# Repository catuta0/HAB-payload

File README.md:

# hab-payload

Carrier PCB for a high-altitude balloon payload. An ESP32 DevKitC V4 (WROOM-32) plugs into the board together with breakout modules for GPS (NEO-8M, I2C or UART header, fit only one), INA260 power monitor, BME280, LSM6DSOX IMU, MAX31855 thermocouple amplifier, RFM95 LoRa radio and an SPI SD card. All modules sit on female headers. The ESP32 is powered from 3.3 V only; its 5 V pin is not connected.

Power comes from a 3S Li-ion pack (9 to 12.6 V) on J1, through a 1.5 A PTC, a 13 V TVS and a P-MOSFET reverse polarity switch, into two TPS62160 bucks at 3.3 V and 5 V. Each buck output goes through a pi filter (ferrite, X7R, solid polymer) with the feedback taken before the ferrite, and the GPS, RFM95 and MAX31855 supplies have their own local ferrite. All capacitors are X7R or solid polymer, with no liquid electrolytics, for operation below 0 C.

The fast SPI lines run on the top layer with 33 ohm series termination at the source (ESP32 for SCK and MOSI, SD module for MISO). Ground is poured on both layers and stitched, SMD pads connect solid to the pour. Test points TP1 to TP4 give VBAT, 3V3, 5V and GND.

Open hardware/pcbgalapagos.kicad_pro in KiCad 10. The project symbol library (galapagos.kicad_sym) and footprint library (galapagos_fp.pretty) are registered relative to the project folder. BOM.csv lists every part with its Mouser link (the breakout modules are bought separately), and docs/firmware_changes.md lists what the firmware has to change for this board.

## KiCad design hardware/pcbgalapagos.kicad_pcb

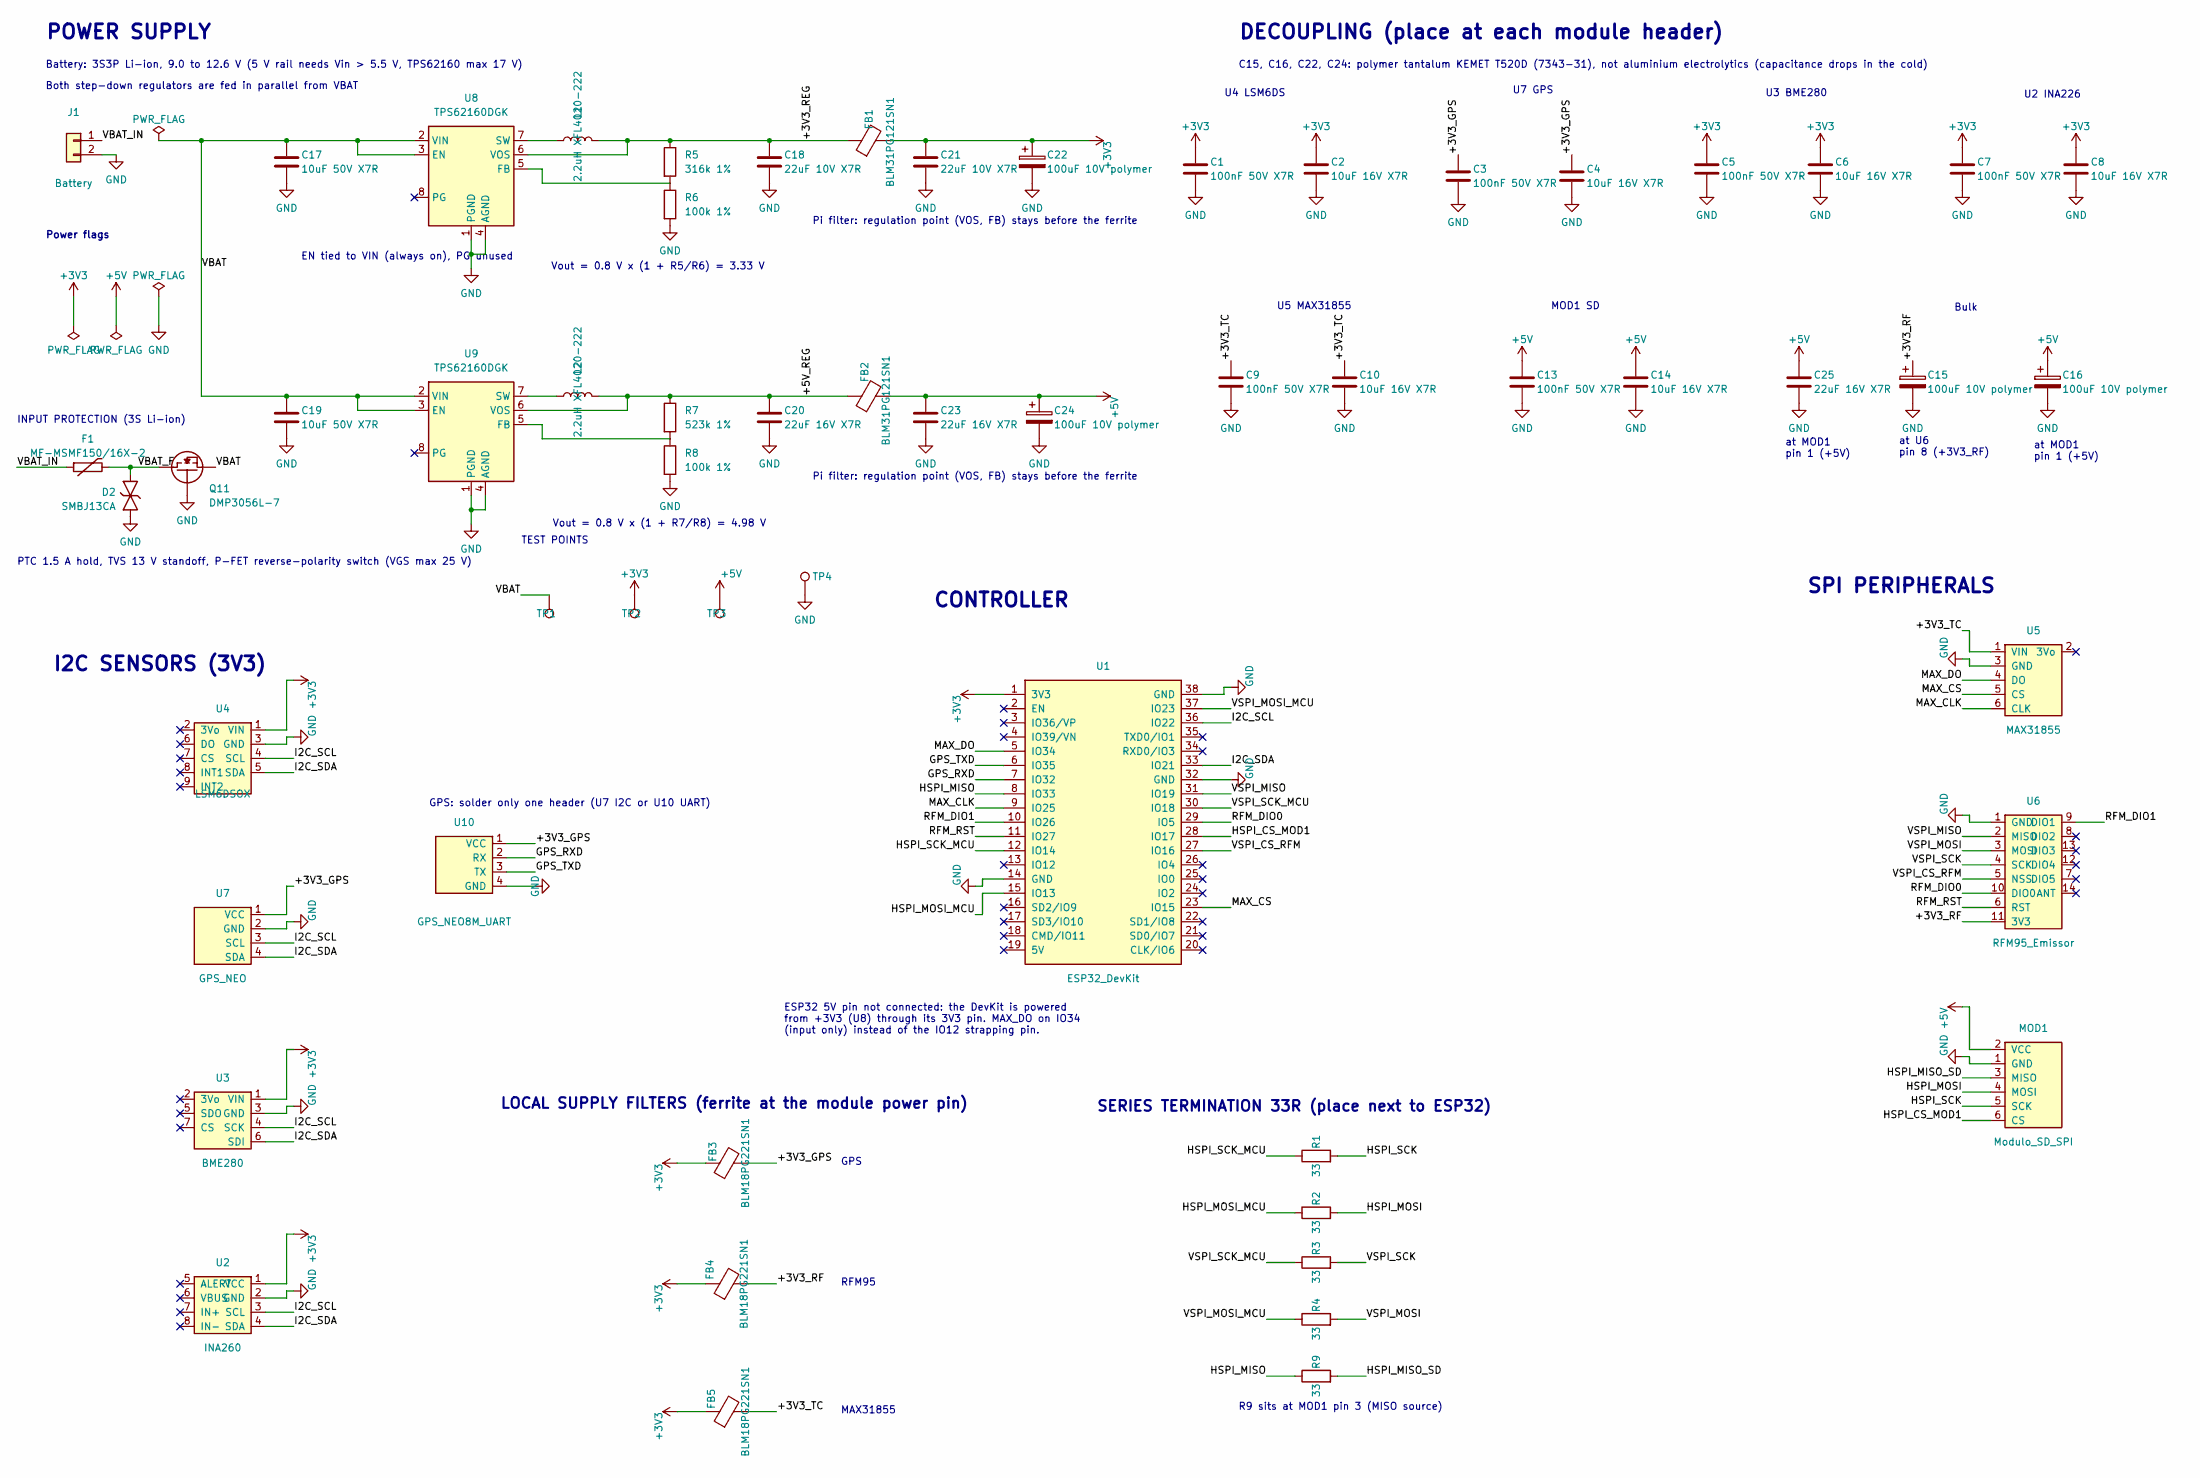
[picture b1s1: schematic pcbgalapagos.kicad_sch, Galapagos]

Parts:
C1, C3, C5, C7, C9, C13: 100nF 50V X7R; C_0805_2012Metric
C2, C4, C6, C8, C10, C14: 10uF 16V X7R; C_0805_2012Metric
C15, C16, C22, C24: 100uF 10V polymer; CP_EIA-7343-31_Kemet-D
C17, C19: 10uF 50V X7R; C_1210_3225Metric
C18, C21: 22uF 10V X7R; C_1206_3216Metric
C20, C23, C25: 22uF 16V X7R; C_1206_3216Metric
D2: SMBJ13CA; D_SMB
F1: MF-MSMF150/16X-2; Fuse_1812_4532Metric
FB1, FB2: BLM31PG121SN1; L_1206_3216Metric
FB3, FB4, FB5: BLM18PG221SN1; L_0603_1608Metric
J1: Battery; JST_XH_B2B-XH-A_1x02_P2.50mm_Vertical
L1, L2: 2.2uH XFL4020-222; L_Coilcraft_XxL4020
MOD1: Modulo_SD_SPI; PinHeader_1x06_P2.54mm_Vertical
Q11: DMP3056L-7; SOT-23
R1, R2, R3, R4, R9: 33; R_0805_2012Metric
R5: 316k 1%; R_0805_2012Metric
R6, R8: 100k 1%; R_0805_2012Metric
R7: 523k 1%; R_0805_2012Metric
TP1, TP2, TP3, TP4: TestPoint; TestPoint_Pad_D1.5mm
U1: ESP32_DevKit; ESP32_DevKitC_V4_38
U2: INA260; Adafruit_INA260_Header
U3: BME280; Adafruit_BME280_Header
U4: LSM6DSOX; Adafruit_LSM6DSOX_Header
U5: MAX31855; Adafruit_MAX31855_Header
U6: RFM95_Emissor; RFM9x_Breakout_attexx
U7: GPS_NEO; GPS_I2C_Header_1x04
U8, U9: TPS62160DGK; MSOP-8_3x3mm_P0.65mm
U10: GPS_NEO8M_UART; GPS_NEO8M_UART_Header_1x04

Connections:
+3V3: C1.1, C2.1, C5.1, C6.1, C7.1, C8.1, C21.1, C22.1, FB1.2, FB3.1, FB4.1, FB5.1, TP2.1, U1.1 (3V3), U2.1 (VCC), U3.1 (VIN), U4.1 (VIN)
+3V3_GPS: C3.1, C4.1, FB3.2, U7.1 (VCC), U10.1 (VCC)
+3V3_REG: C18.1, FB1.1, L1.2, R5.1, U8.6 (VOS)
+3V3_RF: C15.1, FB4.2, U6.11 (3V3)
+3V3_TC: C9.1, C10.1, FB5.2, U5.1 (VIN)
+5V: C13.1, C14.1, C16.1, C23.1, C24.1, C25.1, FB2.2, MOD1.2 (VCC), TP3.1
+5V_REG: C20.1, FB2.1, L2.2, R7.1, U9.6 (VOS)
GND: C1.2, C2.2, C3.2, C4.2, C5.2, C6.2, C7.2, C8.2, C9.2, C10.2, C13.2, C14.2, C15.2, C16.2, C17.2, C18.2, C19.2, C20.2, C21.2, C22.2, C23.2, C24.2, C25.2, D2.2 (A2), J1.2, MOD1.1 (GND), Q11.1 (G), R6.2, R8.2, TP4.1, U1.14 (GND), U1.32 (GND), U1.38 (GND), U2.2 (GND), U3.3 (GND), U4.3 (GND), U5.3 (GND), U6.1 (GND), U7.2 (GND), U8.1 (PGND), U8.4 (AGND), U9.1 (PGND), U9.4 (AGND), U10.4 (GND)
GPS_RXD: U1.7 (IO32), U10.2 (RX)
GPS_TXD: U1.6 (IO35), U10.3 (TX)
HSPI_CS_MOD1: MOD1.6 (CS), U1.28 (IO17)
HSPI_MISO: R9.1, U1.8 (IO33)
HSPI_MISO_SD: MOD1.3 (MISO), R9.2
HSPI_MOSI: MOD1.4 (MOSI), R2.2
HSPI_MOSI_MCU: R2.1, U1.15 (IO13)
HSPI_SCK: MOD1.5 (SCK), R1.2
HSPI_SCK_MCU: R1.1, U1.12 (IO14)
I2C_SCL: U1.36 (IO22), U2.3 (SCL), U3.4 (SCK), U4.4 (SCL), U7.3 (SCL)
I2C_SDA: U1.33 (IO21), U2.4 (SDA), U3.6 (SDI), U4.5 (SDA), U7.4 (SDA)
MAX_CLK: U1.9 (IO25), U5.6 (CLK)
MAX_CS: U1.23 (IO15), U5.5 (CS)
MAX_DO: U1.5 (IO34), U5.4 (DO)
unnamed: R5.2, R6.1, U8.5 (FB)
unnamed: L1.1, U8.7 (SW)
unnamed: R7.2, R8.1, U9.5 (FB)
unnamed: L2.1, U9.7 (SW)
RFM_DIO0: U1.29 (IO5), U6.10 (DIO0)
RFM_DIO1: U1.10 (IO26), U6.9 (DIO1)
RFM_RST: U1.11 (IO27), U6.6 (RST)
VBAT: C17.1, C19.1, Q11.2 (S), TP1.1, U8.2 (VIN), U8.3 (EN), U9.2 (VIN), U9.3 (EN)
VBAT_F: D2.1 (A1), F1.2, Q11.3 (D)
VBAT_IN: F1.1, J1.1
VSPI_CS_RFM: U1.27 (IO16), U6.5 (NSS)
VSPI_MISO: U1.31 (IO19), U6.2 (MISO)
VSPI_MOSI: R4.2, U6.3 (MOSI)
VSPI_MOSI_MCU: R4.1, U1.37 (IO23)
VSPI_SCK: R3.2, U6.4 (SCK)
VSPI_SCK_MCU: R3.1, U1.30 (IO18)

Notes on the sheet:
Vout = 0.8 V x (1 + R5/R6) = 3.33 V
CONTROLLER
RFM95
Bulk
PTC 1.5 A hold, TVS 13 V standoff, P-FET reverse-polarity switch (VGS max 25 V)
Vout = 0.8 V x (1 + R7/R8) = 4.98 V
MAX31855
Power flags
GPS
U2 INA226
at MOD1 pin 1 (+5V)
INPUT PROTECTION (3S Li-ion)
MOD1 SD
SPI PERIPHERALS
SERIES TERMINATION 33R (place next to ESP32)
U7 GPS
U3 BME280
C15, C16, C22, C24: polymer tantalum KEMET T520D (7343-31), not aluminium electrolytics (capacitance drops in the cold)
Battery: 3S3P Li-ion, 9.0 to 12.6 V (5 V rail needs Vin > 5.5 V, TPS62160 max 17 V)
at U6 pin 8 (+3V3_RF)
DECOUPLING (place at each module header)
Both step-down regulators are fed in parallel from VBAT
I2C SENSORS (3V3)
Pi filter: regulation point (VOS, FB) stays before the ferrite
POWER SUPPLY
U5 MAX31855
LOCAL SUPPLY FILTERS (ferrite at the module power pin)
EN tied to VIN (always on), PG unused
U4 LSM6DS
ESP32 5V pin not connected: the DevKit is powered from +3V3 (U8) through its 3V3 pin. MAX_DO on IO34 (input only) instead of the IO12 strapping pin.
GPS: solder only one header (U7 I2C or U10 UART)
R9 sits at MOD1 pin 3 (MISO source)
TEST POINTS

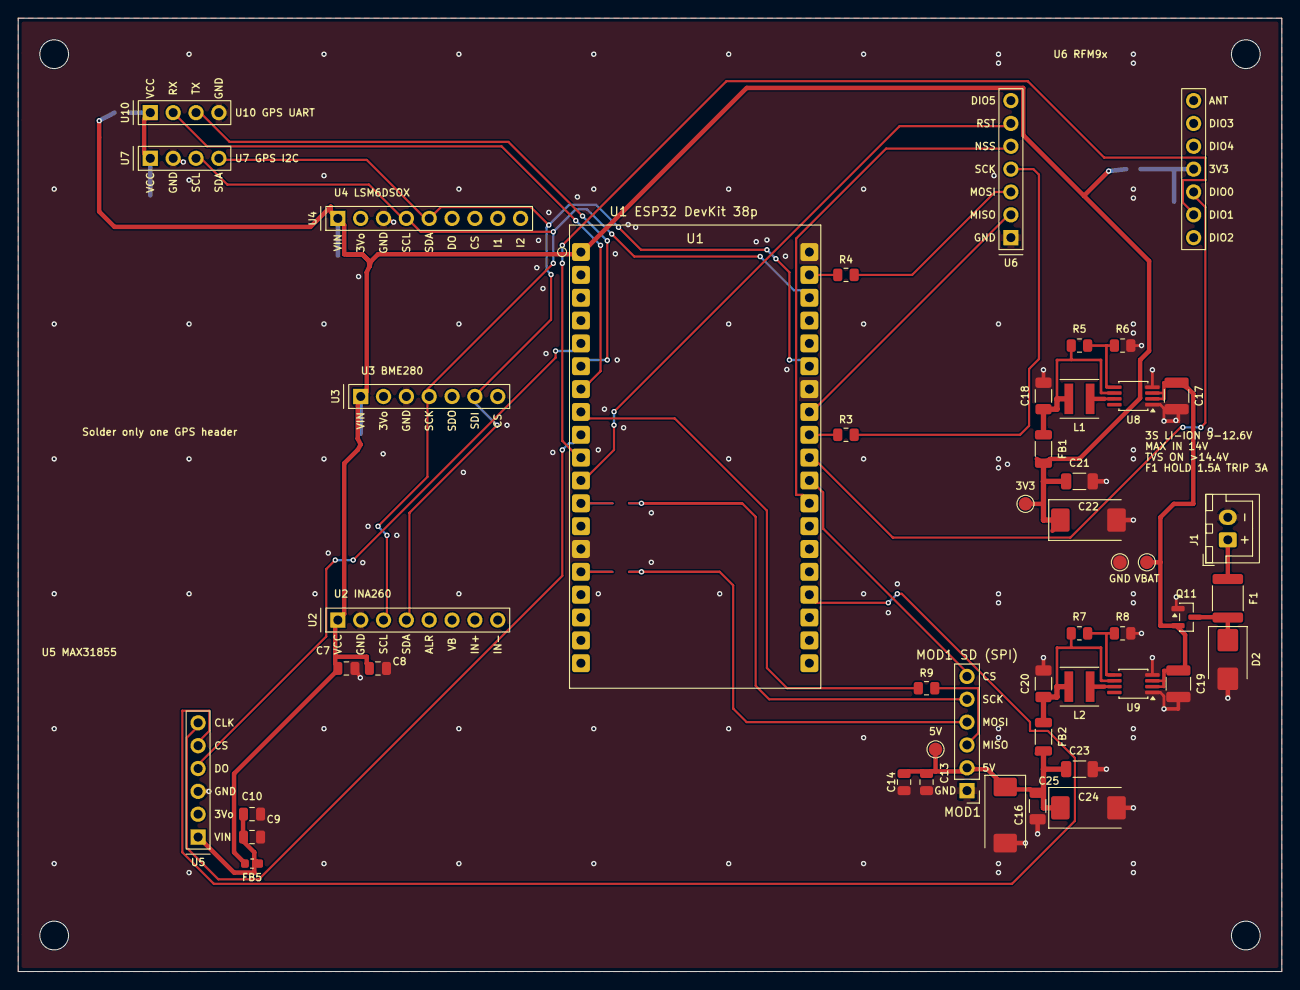
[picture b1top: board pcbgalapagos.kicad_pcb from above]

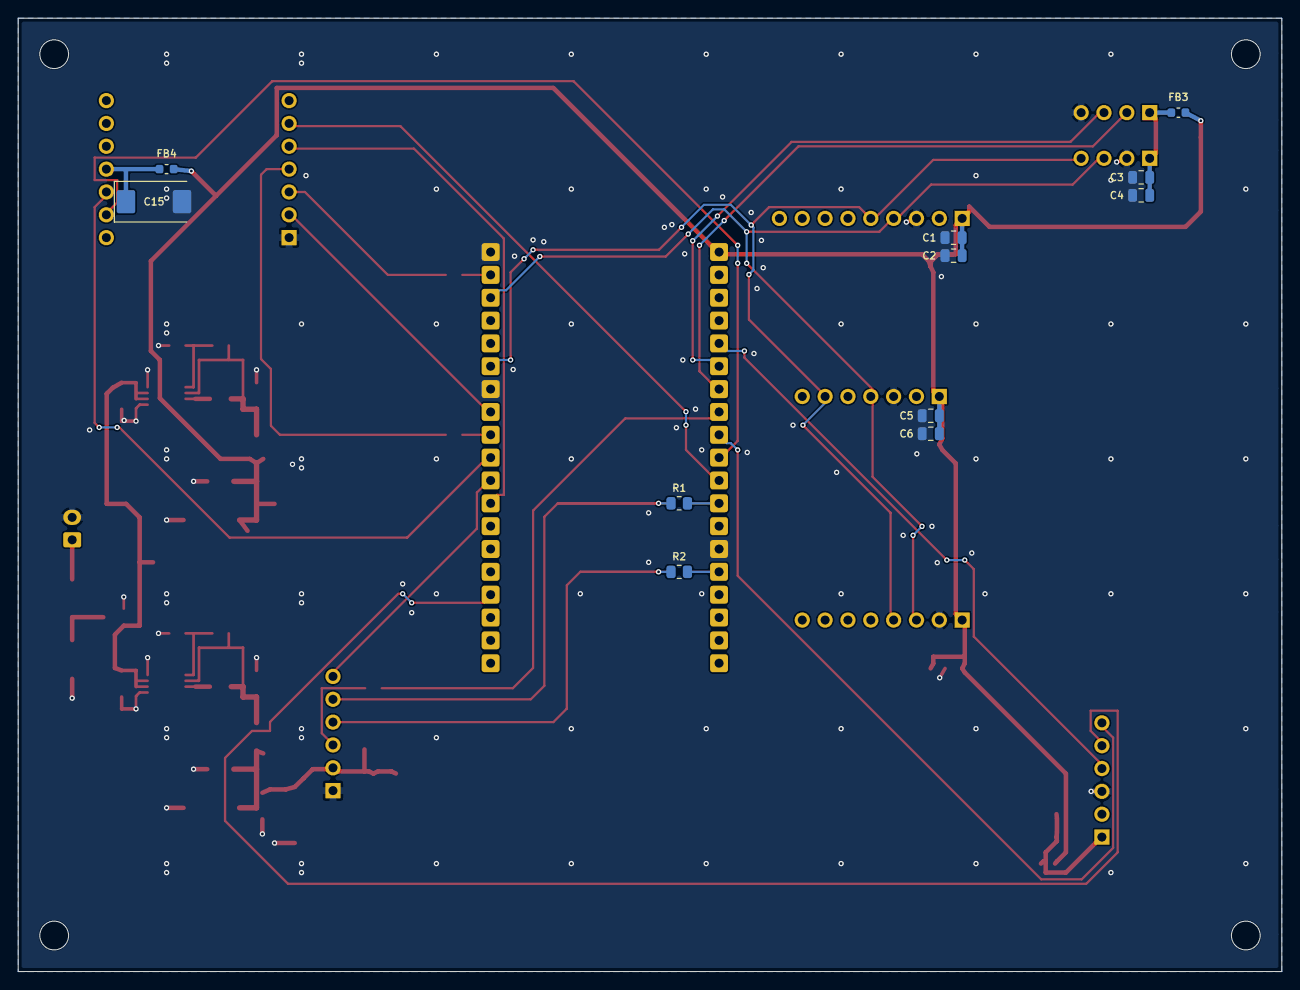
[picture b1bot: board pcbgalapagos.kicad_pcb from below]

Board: 2 copper layers, 140.5 x 106.0 mm, 62 parts (11 on the bottom side), 38 nets.

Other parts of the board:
H1, H2, H3, H4: MountingHole_3.2mm_M3

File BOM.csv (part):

References,Qty,Description,Package,Manufacturer,MPN,Mouser PN,Mouser link,Unit price,Currency,Line total,Price source,Notes
"U8,U9",2,TPS62160DGK step-down 3-17V 1A,VSSOP-8 (MSOP-8),Texas Instruments,TPS62160DGKR,595-TPS62160DGKR,https://www.mouser.com/ProductDetail/595-TPS62160DGKR,1.56,EUR,3.12,"pt.mouser.com 2026-10-28, qty 1",3.3 V and 5 V bucks
"L1,L2",2,2.2uH 20% shielded power inductor,4x4 mm (XFL4020),Coilcraft,XFL4020-222MEC,994-XFL4020-222MEC,https://www.mouser.com/ProductDetail/994-XFL4020-222MEC,1.98,EUR,3.96,"pt.mouser.com 2026-10-28, qty 1","Out of stock at Mouser on 2026-10-27; alternative Wurth 74438357022 (710-74438357022, 4.1x4.1 mm) needs its land pattern checked against the XFL4020 footprint"
F1,1,PTC resettable fuse 1.5A hold 3A trip 16V,1812,Bourns,MF-MSMF150/16X-2,652-MF-MSMF150/16X-2,https://www.mouser.com/ProductDetail/652-MF-MSMF150%2F16X-2,0.525,EUR,0.53,"pt.mouser.com 2026-10-28, qty 1",Battery input protection
D2,1,TVS 13V standoff bidirectional 600W,SMB (DO-214AA),Littelfuse,SMBJ13CA,576-SMBJ13CA,https://www.mouser.com/ProductDetail/576-SMBJ13CA,0.525,EUR,0.53,"pt.mouser.com 2026-10-28, qty 1",Battery input protection
Q11,1,P-MOSFET 30V 4.3A,SOT-23,Diodes Incorporated,DMP3056L-7,621-DMP3056L-7,https://www.mouser.com/ProductDetail/621-DMP3056L-7,0.542,EUR,0.54,"pt.mouser.com 2026-10-28, qty 1",Reverse polarity switch
R5,1,316k 1% 0805,0805,Yageo,RC0805FR-07316KL,603-RC0805FR-07316KL,https://www.mouser.com/ProductDetail/603-RC0805FR-07316KL,0.086,EUR,0.09,"pt.mouser.com 2026-10-28, qty 1",3.3 V feedback
R7,1,523k 1% 0805,0805,Yageo,RC0805FR-07523KL,603-RC0805FR-07523KL,https://www.mouser.com/ProductDetail/603-RC0805FR-07523KL,0.086,EUR,0.09,"pt.mouser.com 2026-10-28, qty 1",5 V feedback
"R6,R8",2,100k 1% 0805,0805,Yageo,RC0805FR-07100KL,603-RC0805FR-07100KL,https://www.mouser.com/ProductDetail/603-RC0805FR-07100KL,0.086,EUR,0.17,"pt.mouser.com 2026-10-28, qty 1",Feedback bottom
"R1,R2,R3,R4,R9",5,33R 1% 0805,0805,Yageo,RC0805FR-0733RL,603-RC0805FR-0733RL,https://www.mouser.com/ProductDetail/603-RC0805FR-0733RL,0.086,EUR,0.43,"pt.mouser.com 2026-10-28, qty 1",SPI series termination (R9 on SD MISO at MOD1)
"C17,C19",2,10uF 50V X7R,1210,TDK,C3225X7R1H106K250AC,810-C3225X7R1H106250,https://www.mouser.com/ProductDetail/810-C3225X7R1H106250,0.877,EUR,1.75,"pt.mouser.com 2026-10-28, qty 1",Buck input
"C18,C20,C21,C23,C25",5,22uF 16V X7R,1206,Murata,GRM31CZ71C226ME15L,81-GRM31CZ71C226ME5L,https://www.mouser.com/ProductDetail/81-GRM31CZ71C226ME5L,0.912,EUR,4.56,"pt.mouser.com 2026-10-28, qty 1","3.3 V and 5 V buck outputs, pi filters, SD bulk (16 V part used on 3.3 V too for DC-bias margin)"
"C15,C16,C22,C24",4,100uF 10V polymer tantalum 55mOhm,7343-31 (D),KEMET,T520D107M010ATE055,80-T520D107M10E55,https://www.mouser.com/ProductDetail/80-T520D107M10E55,1.53,EUR,6.12,"pt.mouser.com 2026-10-28, qty 1","Solid polymer, -55 to +105 C"
"C2,C4,C6,C8,C10,C14",6,10uF 16V X7R,0805,Samsung,CL21B106KOQNNNE,187-CL21B106KOQNNNE,https://www.mouser.com/ProductDetail/187-CL21B106KOQNNNE,0.421,EUR,2.53,"pt.mouser.com 2026-10-28, qty 1",Module local decoupling
"C1,C3,C5,C7,C9,C13",6,100nF 50V X7R,0805,Samsung,CL21B104KBCNNNC,187-CL21B104KBCNNNC,https://www.mouser.com/ProductDetail/187-CL21B104KBCNNNC,0.086,EUR,0.52,"pt.mouser.com 2026-10-28, qty 1",Module local decoupling
"FB1,FB2",2,Ferrite 120R@100MHz 3.5A,1206,Murata,BLM31PG121SN1L,81-BLM31PG121SN1L,https://www.mouser.com/ProductDetail/81-BLM31PG121SN1L,0.43,EUR,0.86,"pt.mouser.com 2026-10-28, qty 1",Buck pi filter
"FB3,FB4,FB5",3,Ferrite 220R@100MHz 1.4A,0603,Murata,BLM18PG221SN1D,81-BLM18PG221SN1D,https://www.mouser.com/ProductDetail/81-BLM18PG221SN1D,0.12,EUR,0.36,"pt.mouser.com 2026-10-28, qty 1","GPS, RFM95 and MAX31855 supply"
J1,1,JST XH 2-pin vertical,2.5 mm,JST,B2B-XH-A(LF)(SN),306-B2BXHALFSNP,https://www.mouser.com/ProductDetail/306-B2BXHALFSNP,0.086,EUR,0.09,"pt.mouser.com 2026-10-28, qty 1",Battery input
"U1,U3,U4,U6",4,Female header 1x20 2.54 mm,THT,Wurth Elektronik,61302011821,710-61302011821,https://www.mouser.com/ProductDetail/710-61302011821,0.8,EUR,3.2,"pt.mouser.com 2026-10-28, qty 1","Cut to length (each cut loses one position): two strips of 19 for the ESP32, one strip for U4 (9) + U3 (7), one strip for the two 1x7 rows of U6"
U2,1,Female header 1x8 2.54 mm,THT,Wurth Elektronik,61300811821,710-61300811821,https://www.mouser.com/ProductDetail/710-61300811821,0.353,EUR,0.35,"pt.mouser.com 2026-10-28, qty 1",INA260
"U5,MOD1",2,Female header 1x6 2.54 mm,THT,Wurth Elektronik,61300611821,710-61300611821,https://www.mouser.com/ProductDetail/710-61300611821,0.258,EUR,0.52,"pt.mouser.com 2026-10-28, qty 1",MAX31855 and SD module
"U7,U10",2,Female header 1x4 2.54 mm,THT,Wurth Elektronik,61300411821,710-61300411821,https://www.mouser.com/ProductDetail/710-61300411821,0.361,EUR,0.72,"pt.mouser.com 2026-10-28, qty 1",GPS I2C and GPS UART; solder only the one in use
"TP1,TP2,TP3,TP4",0,Test pad 1.5 mm,SMD pad,,,,not applicable (part of the PCB),,,,,"Bare copper pads, nothing to buy"
"H1,H2,H3,H4",0,M3 mounting hole,3.2 mm,,,,not applicable (part of the PCB),,,,,Nothing to buy
U1,1,ESP32-DevKitC V4 38-pin with ESP32-WROOM-32 (not WROVER: IO16/IO17 are used),module,Espressif,ESP32-DevKitC-32E,356-ESP32-DEVKITC32E,https://www.mouser.com/ProductDetail/356-ESP32-DEVKITC32E,8.78,EUR,8.78,pt.mouser.com 356-ESP32-DEVKITC32E,Bought separately; powered from its 3V3 pin
U2,1,Adafruit INA260 breakout,module,Adafruit,4226,,https://www.adafruit.com/product/4226,9.95,USD,9.95,adafruit.com,Bought separately; VBUS/IN+/IN- wired off-board to the battery
U3,1,Adafruit BME280 breakout,module,Adafruit,2652,,https://www.adafruit.com/product/2652,14.95,USD,14.95,adafruit.com,Bought separately
U4,1,Adafruit LSM6DSOX breakout,module,Adafruit,4438,,https://www.adafruit.com/product/4438,11.95,USD,11.95,adafruit.com,Bought separately
U5,1,Adafruit MAX31855 thermocouple breakout,module,Adafruit,269,,https://www.adafruit.com/product/269,14.95,USD,14.95,adafruit.com,Bought separately; needs a type K thermocouple
U6,1,RFM95W LoRa module 868 MHz,module,HopeRF / attexx,RFM95W-868S2,,https://soselectronic.com/en/products/rfm95w-868-s2,6.98,EUR,6.98,"soselectronic.com 2026-10-28, excl. VAT",Mounted on the attexx breakout PCB (row below)
U6 PCB,1,attexx rfm9x_breakout_board rev 1b (bare PCB),PCB,AISLER,,,https://aisler.net/p/BNYBJOFL,,,,price on aisler.net (sold in sets of 3),Design: github.com/attexx/rfm9x_breakout_board; also needs C1 10uF 0805 (use a spare CL21B106KOQNNNE)
U6 J1,1,SMA female edge-launch jack 50 Ohm for 1.6 mm (0.062 in) PCB,Edge mount,TE Connectivity / Linx,CONSMA003.062-G,712-CONSMA003.062-G,https://www.mouser.com/ProductDetail/712-CONSMA003.062-G,3.84,EUR,3.84,pt.mouser.com 2026-10-28,"Antenna connector on the RFM95 breakout; matches its footprint (centre 1.52 mm, ground legs at 2.54 mm); takes the SMA male of the antenna (not RP-SMA)"
U7 or U10,1,GPS NEO-8M breakout (I2C on U7 or UART on U10),module,,,,https://www.botnroll.com/en/gps-gnss/5479-uart-gps-neo-8m-w-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,18.9,EUR,18.9,botnroll.com 2026-10-28 (UART version; any NEO-8M breakout with the same pin order works),Fit only one; check the pin order matches VCC RX TX GND (UART) or VCC GND SCL SDA (I2C) before soldering the header
MOD1,1,AZ-Delivery SPI micro SD card module,module,AZ-Delivery,,,https://www.az-delivery.de/en/products/copy-of-spi-reader-mi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,4.49,EUR,4.49,az-delivery.de,Bought separately; powered from 5 V; use an industrial-temperature card
ANT1,1,"868 MHz half-wave dipole antenna 3.2 dBi peak 93% efficiency, -40 to +85 C","SMA male, 389 mm",Taoglas,TI.18.3113,960-TI.18.3113,https://www.mouser.com/ProductDetail/960-TI.18.3113,13.27,EUR,13.27,pt.mouser.com 2026-10-28,"Plugs into the SMA on the RFM95 breakout; no ground plane needed; hinged, tape it straight for flight"
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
